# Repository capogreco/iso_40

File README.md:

# Tender Mending Sender

staggered 40 with ISO enter

say what you mean, do what you love, and fucking send it

## Layout

40-key staggered keyboard with ISO Enter, 6u spacebar, and ATmega32U4.

### Layer 0 — Default

| | | | | | | | | | | | |
|---|---|---|---|---|---|---|---|---|---|---|---|
| Esc | Q | W | E | R | T | Y | U | I | O | P | Enter (ISO) |
| Tab/Ctrl | A | S | D | F | G | H | J | K | L | ' | |
| Shift | Z | X | C | V | B | N | M | , | . | / | Fn2 |
| | Fn1 | Super | | | Space (6u) | | | | Bksp | AltGr | |

### Layer 1 — Numbers / Punctuation (Fn1)

| | | | | | | | | | | | |
|---|---|---|---|---|---|---|---|---|---|---|---|
| | | | | | | | 7 | 8 | 9 | 0 | |
| | \` | \\ | [ | ] | - | = | 4 | 5 | 6 | ; | |
| | | | | | , | . | 1 | 2 | 3 | | |
| | | | | | | | | | | | |

### Layer 2 — Navigation / Function (Fn2)

| | | | | | | | | | | | |
|---|---|---|---|---|---|---|---|---|---|---|---|
| | F1 | F2 | F3 | F4 | Vol+ | | | | | PrtScn | |
| | F5 | F6 | F7 | F8 | Vol- | | PgUp | Home | Up | End | |
| | F9 | F10 | F11 | F12 | Mute | | PgDn | Left | Down | Right | |
| | | | | | | | | | Del | | |

## Firmware

QMK firmware source is in `iso_40/`. To compile and flash:

```
qmk compile -kb iso_40 -km default
qmk flash -kb iso_40 -km default
```

Requires `avr-gcc`, `avrdude`, and the QMK CLI. The keyboard directory needs to be copied into your `qmk_firmware/keyboards/` tree before compiling.

Bootloader is Caterina (Pro Micro compatible) — double-tap reset to enter bootloader mode.

## PCB

Designed in KiCad. Gerber files for manufacturing are in `gerbers/`.

Switch footprints from [ai03 MX_Alps_Hybrid](https://github.com/ai03-2725/MX_Alps_Hybrid) and [random-keyboard-parts](https://github.com/ai03-2725/random-keyboard-parts.pretty) (included as git submodules).

## License

[MIT](LICENSE)

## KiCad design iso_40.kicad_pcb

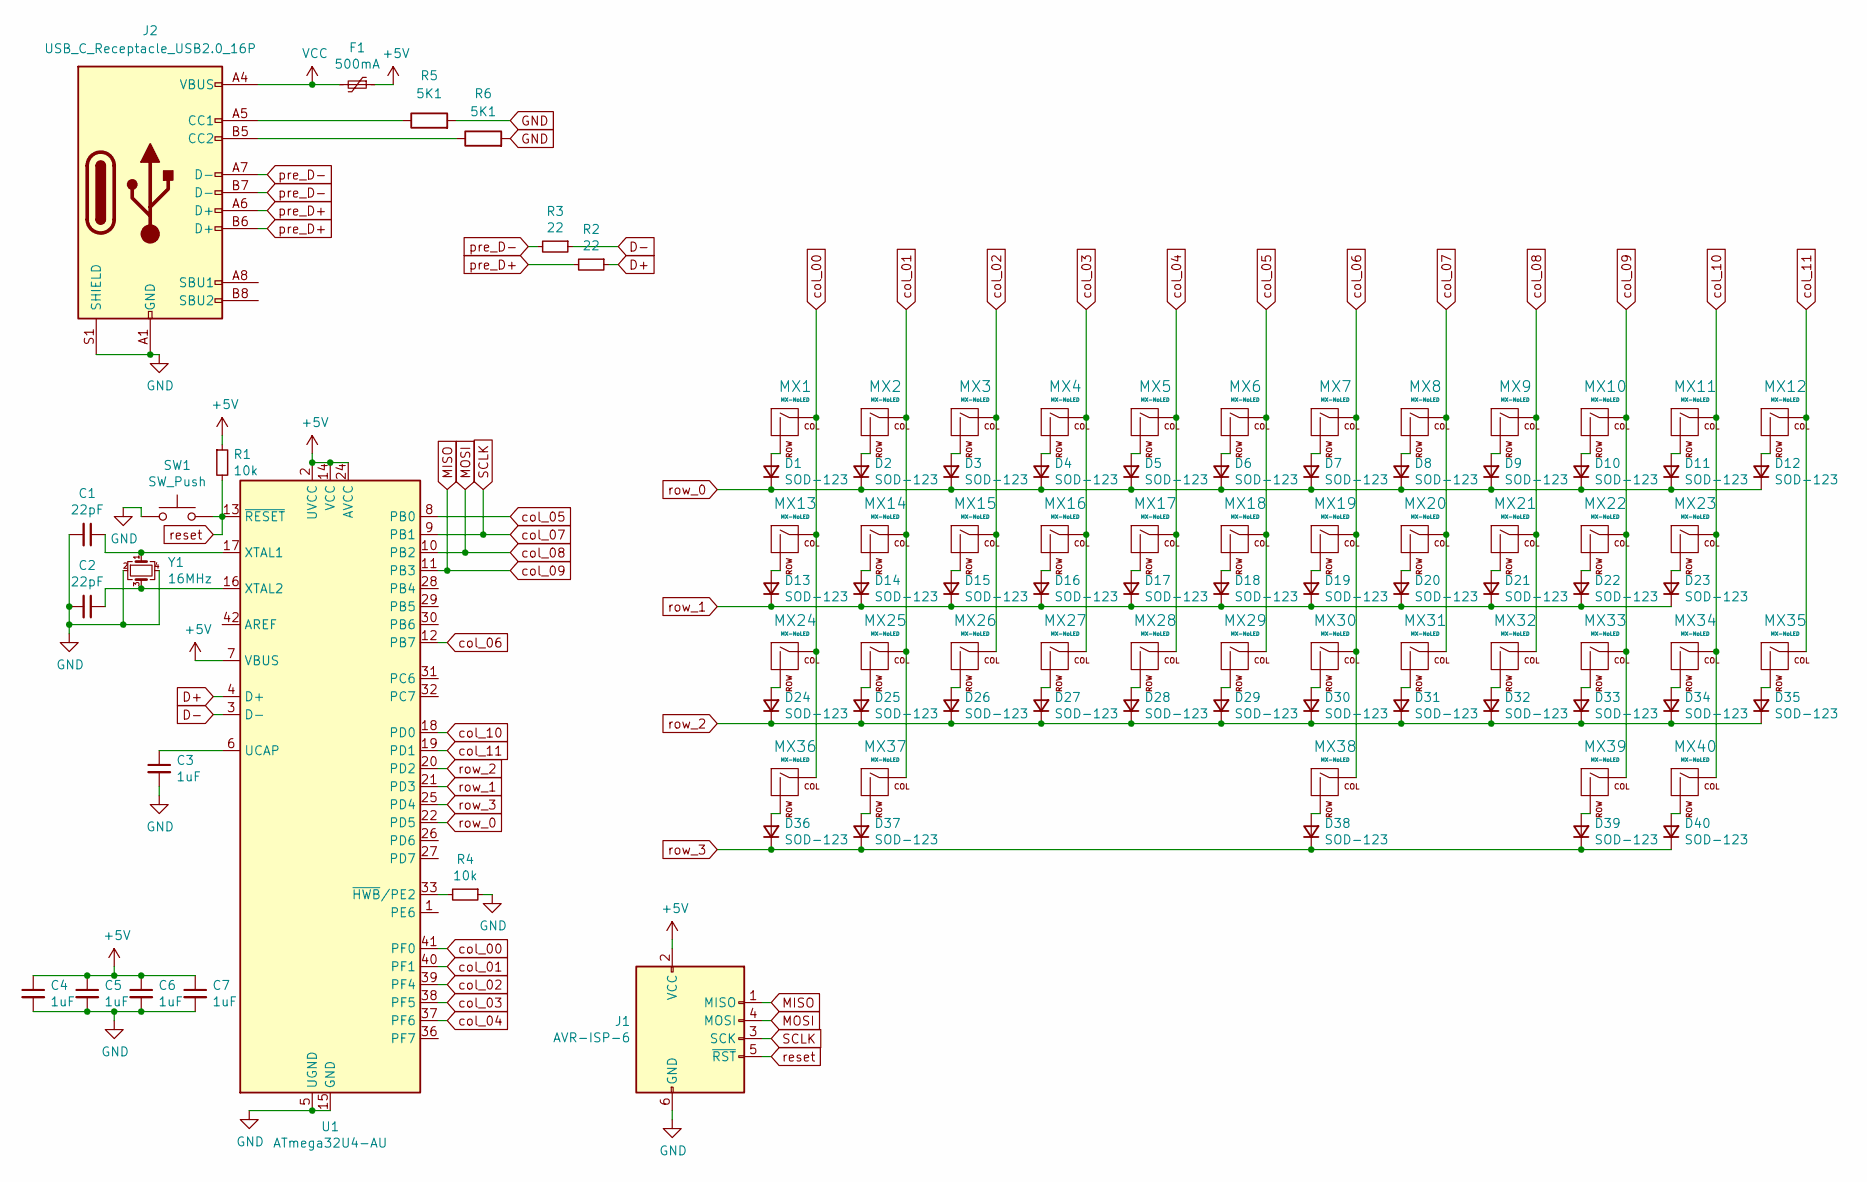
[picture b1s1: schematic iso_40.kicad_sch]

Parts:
C1, C2: 22pF; C_0805_2012Metric
C3, C4, C5, C6, C7: 1uF; C_0805_2012Metric
D1, D2, D3, D4, D5, D6, D7, D8, D9, D10, D11, D12, D13, D14, D15, D16, D17, D18, D19, D20, D21, D22, D23, D24, D25, D26, D27, D28, D29, D30, D31, D32, D33, D34, D35, D36, D37, D38, D39, D40: SOD-123; D_SOD-123
F1: 500mA; Fuse_1206_3216Metric
J1: AVR-ISP-6; PinHeader_2x03_P1.27mm_Vertical_SMD
J2: USB_C_Receptacle_USB2.0_16P; USB_C_Receptacle_GCT_USB4110
MX1, MX2, MX3, MX4, MX5, MX6, MX7, MX8, MX9, MX10, MX11, MX14, MX15, MX16, MX17, MX18, MX19, MX20, MX21, MX22, MX23, MX25, MX26, MX27, MX28, MX29, MX30, MX31, MX32, MX33, MX34, MX35, MX36, MX40: MX-NoLED; MXOnly-1U-NoLED
MX12: MX-NoLED; MXOnly-ISO
MX13: MX-NoLED; MXOnly-1.25U-NoLED
MX24, MX37, MX39: MX-NoLED; MXOnly-1.5U-NoLED
MX38: MX-NoLED; MXOnly-6U-NoLED
R1, R4: 10k; R_0805_2012Metric
R2, R3: 22; R_0805_2012Metric
R5, R6: 5K1
SW1: SW_Push; SKQG-1155865
U1: ATmega32U4-AU; TQFP-44_10x10mm_P0.8mm
Y1: 16MHz; Crystal_SMD_3225-4Pin_3.2x2.5mm

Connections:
+5V: C4.1, C5.1, C6.1, C7.1, F1.1, J1.2 (VCC), R1.1, U1.2 (UVCC), U1.7 (VBUS), U1.14 (VCC), U1.24 (AVCC), U1.34 (VCC), U1.44 (AVCC)
D+: R2.1, U1.4 (D+)
D-: R3.1, U1.3 (D-)
GND: C1.2, C2.2, C3.2, C4.2, C5.2, C6.2, C7.2, J1.6 (GND), J2.A1 (GND), J2.A12 (GND), J2.B1 (GND), J2.B12 (GND), J2.S1 (SHIELD), R4.1, SW1.1, U1.5 (UGND), U1.15 (GND), U1.23 (GND), U1.35 (GND), U1.43 (GND), Y1.2, Y1.4
MISO: J1.1 (MISO), MX10.1 (COL), MX22.1 (COL), MX33.1 (COL), MX39.1 (COL), U1.11 (PB3)
MOSI: J1.4 (MOSI), MX9.1 (COL), MX21.1 (COL), MX32.1 (COL), U1.10 (PB2)
unnamed: D1.2 (A), MX1.2 (ROW)
unnamed: D2.2 (A), MX2.2 (ROW)
unnamed: D3.2 (A), MX3.2 (ROW)
unnamed: D4.2 (A), MX4.2 (ROW)
unnamed: D5.2 (A), MX5.2 (ROW)
unnamed: D6.2 (A), MX6.2 (ROW)
unnamed: D7.2 (A), MX7.2 (ROW)
unnamed: D8.2 (A), MX8.2 (ROW)
unnamed: D9.2 (A), MX9.2 (ROW)
unnamed: D10.2 (A), MX10.2 (ROW)
unnamed: D11.2 (A), MX11.2 (ROW)
unnamed: D12.2 (A), MX12.2 (ROW)
unnamed: D13.2 (A), MX13.2 (ROW)
unnamed: D14.2 (A), MX14.2 (ROW)
unnamed: D15.2 (A), MX15.2 (ROW)
unnamed: D16.2 (A), MX16.2 (ROW)
unnamed: D17.2 (A), MX17.2 (ROW)
unnamed: D18.2 (A), MX18.2 (ROW)
unnamed: D19.2 (A), MX19.2 (ROW)
unnamed: D20.2 (A), MX20.2 (ROW)
unnamed: D21.2 (A), MX21.2 (ROW)
unnamed: D22.2 (A), MX22.2 (ROW)
unnamed: D23.2 (A), MX23.2 (ROW)
unnamed: D24.2 (A), MX24.2 (ROW)
unnamed: D25.2 (A), MX25.2 (ROW)
unnamed: D26.2 (A), MX26.2 (ROW)
unnamed: D27.2 (A), MX27.2 (ROW)
unnamed: D28.2 (A), MX28.2 (ROW)
unnamed: D29.2 (A), MX29.2 (ROW)
unnamed: D30.2 (A), MX30.2 (ROW)
unnamed: D31.2 (A), MX31.2 (ROW)
unnamed: D32.2 (A), MX32.2 (ROW)
unnamed: D33.2 (A), MX33.2 (ROW)
unnamed: D34.2 (A), MX34.2 (ROW)
unnamed: D35.2 (A), MX35.2 (ROW)
unnamed: D36.2 (A), MX36.2 (ROW)
unnamed: D37.2 (A), MX37.2 (ROW)
unnamed: D38.2 (A), MX38.2 (ROW)
unnamed: D39.2 (A), MX39.2 (ROW)
unnamed: D40.2 (A), MX40.2 (ROW)
unnamed: J2.A5 (CC1), R5.1
unnamed: J2.B5 (CC2), R6.1
unnamed: R5.2, R6.2
unnamed: C3.1, U1.6 (UCAP)
unnamed: C1.1, U1.17 (XTAL1), Y1.1
unnamed: C2.1, U1.16 (XTAL2), Y1.3
unnamed: R4.2, U1.33 (~HWB/PE2)
SCLK: J1.3 (SCK), MX8.1 (COL), MX20.1 (COL), MX31.1 (COL), U1.9 (PB1)
VCC: F1.2, J2.A4 (VBUS), J2.A9 (VBUS), J2.B4 (VBUS), J2.B9 (VBUS)
col_00: MX1.1 (COL), MX13.1 (COL), MX24.1 (COL), MX36.1 (COL), U1.41 (PF0)
col_01: MX2.1 (COL), MX14.1 (COL), MX25.1 (COL), MX37.1 (COL), U1.40 (PF1)
col_02: MX3.1 (COL), MX15.1 (COL), MX26.1 (COL), U1.39 (PF4)
col_03: MX4.1 (COL), MX16.1 (COL), MX27.1 (COL), U1.38 (PF5)
col_04: MX5.1 (COL), MX17.1 (COL), MX28.1 (COL), U1.37 (PF6)
col_05: MX6.1 (COL), MX18.1 (COL), MX29.1 (COL), U1.8 (PB0)
col_06: MX7.1 (COL), MX19.1 (COL), MX30.1 (COL), MX38.1 (COL), U1.12 (PB7)
col_10: MX11.1 (COL), MX23.1 (COL), MX34.1 (COL), MX40.1 (COL), U1.18 (PD0)
col_11: MX12.1 (COL), MX35.1 (COL), U1.19 (PD1)
pre_D+: J2.A6 (D+), J2.B6 (D+), R2.2
pre_D-: J2.A7 (D-), J2.B7 (D-), R3.2
reset: J1.5 (~RST), R1.2, SW1.2, U1.13 (~RESET)
row_0: D1.1 (K), D2.1 (K), D3.1 (K), D4.1 (K), D5.1 (K), D6.1 (K), D7.1 (K), D8.1 (K), D9.1 (K), D10.1 (K), D11.1 (K), D12.1 (K), U1.22 (PD5)
row_1: D13.1 (K), D14.1 (K), D15.1 (K), D16.1 (K), D17.1 (K), D18.1 (K), D19.1 (K), D20.1 (K), D21.1 (K), D22.1 (K), D23.1 (K), U1.21 (PD3)
row_2: D24.1 (K), D25.1 (K), D26.1 (K), D27.1 (K), D28.1 (K), D29.1 (K), D30.1 (K), D31.1 (K), D32.1 (K), D33.1 (K), D34.1 (K), D35.1 (K), U1.20 (PD2)
row_3: D36.1 (K), D37.1 (K), D38.1 (K), D39.1 (K), D40.1 (K), U1.25 (PD4)

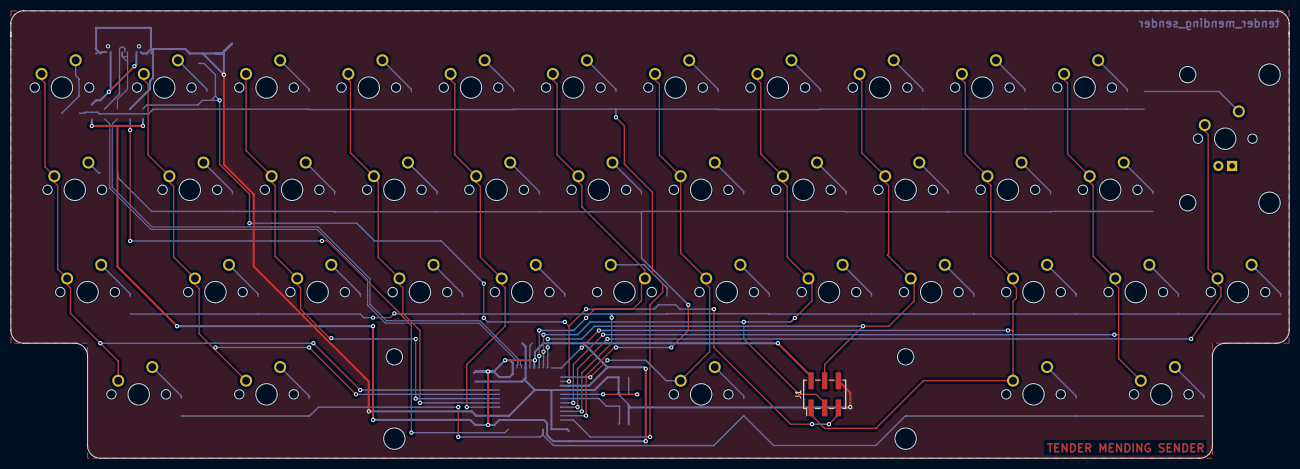
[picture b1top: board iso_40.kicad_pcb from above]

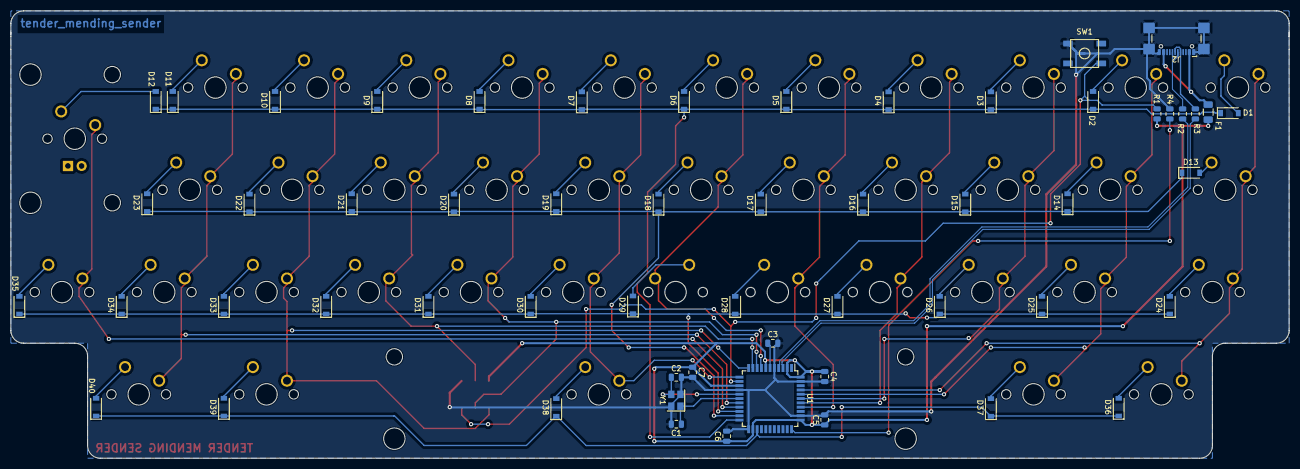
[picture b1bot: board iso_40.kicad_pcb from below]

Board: 2 copper layers, 238.1 x 83.3 mm, 97 parts (57 on the bottom side), 68 nets.

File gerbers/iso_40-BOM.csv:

Comment,Designator,Footprint,LCSC Part #
1N4148W,"D1,D2,D3,D4,D5,D6,D7,D8,D9,D10,D11,D12,D13,D14,D15,D16,D17,D18,D19,D20,D21,D22,D23,D24,D25,D26,D27,D28,D29,D30,D31,D32,D33,D34,D35,D36,D37,D38,D39,D40",D_SOD-123,C84367
22pF,"C1,C2",C_0805_2012Metric,C1804
1uF,"C3,C4,C5,C6,C7",C_0805_2012Metric,C28323
500mA,F1,Fuse_1206_3216Metric,C70074
10k,"R1,R4",R_0805_2012Metric,C17414
22,"R2,R3",R_0805_2012Metric,C17520
SKQGABE010,SW1,SKQG-1155865,C115351
ATmega32U4-AU,U1,TQFP-44_10x10mm_P0.8mm,C44854
16MHz,Y1,Crystal_SMD_3225-4Pin_3.2x2.5mm,C13738
AVR-ISP-6,J1,PinHeader_2x03_P2.54mm_Vertical_SMD,C77761
USB4110-GF-A,J2,USB_C_Receptacle_GCT_USB4110,C5143397

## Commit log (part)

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2020-07-19 ai03 submodules
2020-07-19 component and footprint libraries
2020-07-19 MCU zone
2020-07-19 layout png
2020-07-19 layout png (fixed)
2020-07-21 pcb routed
2020-07-26 review
2020-07-26 ISP header added
2025-12-11 name change
    Updated project name and removed potential names section.
2025-12-11 Update header from 'objet petit a' to 'a petite object'
2025-12-11 Update README title and remove extra text
2025-12-11 updated .png
2025-12-11 updated .png filename
2025-12-18 rename, qmk_firmware folder
2025-12-18 deleted percentage symbol
2025-12-18 deleted "an"
2025-12-18 correct order say / do / send
2026-01-12 pcb changes, etc
